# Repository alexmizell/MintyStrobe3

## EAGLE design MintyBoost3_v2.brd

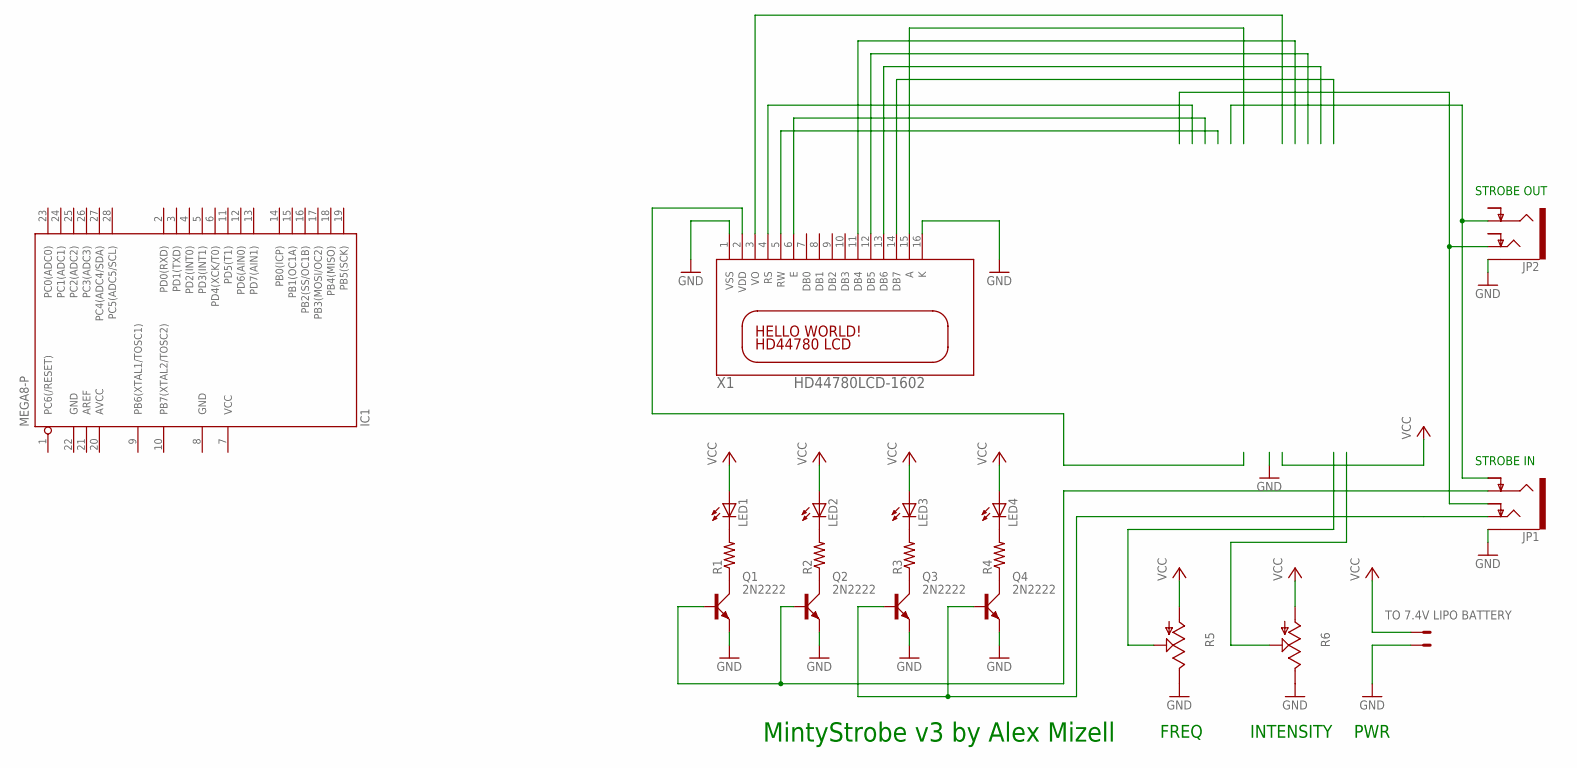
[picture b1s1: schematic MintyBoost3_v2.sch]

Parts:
+5V: 22-23-2021; MPN TO 7.4V LIPO BATTERY
IC1: MEGA8-P; DIL28-3
JP1, JP2: AUDIO-JACK5-.25-VERT-TRS; AUDIO-JACK-.25-INCH-VERT-PTH
LED1, LED2, LED3, LED4: LEDLZR181; LZR181
Q1, Q2, Q3, Q4: 2N2222; TO18A
R1, R2, R3, R4: R-US_0207/10; 0207/10
R5, R6: TRIM_US-S64W; S64W
X1: HD44780LCD-1602; LCD1602

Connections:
AVCC: IC1.20 (AVCC)
GND: +5V.2, IC1.8 (GND), IC1.22 (GND), JP1.SLEEVE (EARTH), JP2.SLEEVE (EARTH), Q1.E, Q2.E, Q3.E, Q4.E, R5.E, R6.E, X1.1 (VSS), X1.16 (K)
unnamed: Q1.C, R1.1
unnamed: Q2.C, R2.1
unnamed: Q3.C, R3.1
unnamed: Q4.C, R4.1
unnamed: LED1.K (C), R1.2
unnamed: LED2.K (C), R2.2
unnamed: LED3.K (C), R3.2
unnamed: LED4.K (C), R4.2
unnamed: JP1.RING, Q1.B, Q2.B
unnamed: JP1.TIP-NORM, JP2.TIP
unnamed: JP1.RING-NORM, JP2.RING
unnamed: JP1.TIP, Q3.B, Q4.B
VCC: +5V.1, IC1.7 (VCC), LED1.A, LED2.A, LED3.A, LED4.A, R5.A, R6.A
VDD: X1.2 (VDD)

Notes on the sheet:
FREQ
INTENSITY
PWR
MintyStrobe v3 by Alex Mizell
STROBE IN
STROBE OUT

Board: 2 copper layers, 19 parts (0 on the bottom side), 14 nets, no tracks yet.

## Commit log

2018-04-26 MintyStrobev3 initial up
    Initial upload
2018-06-26 major update
    180623 Changed to rotary encoders and I2C display
    180626 Added duty cycle adjustment, strobe enable/disable, fine adjust mode and auto-dimming backlight

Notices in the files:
parts and their libraries:
SparkFun-Connectors: Licensing: Creative Commons ShareAlike 4.0 International - https://creativecommons.org/licenses/by-sa/4.0
